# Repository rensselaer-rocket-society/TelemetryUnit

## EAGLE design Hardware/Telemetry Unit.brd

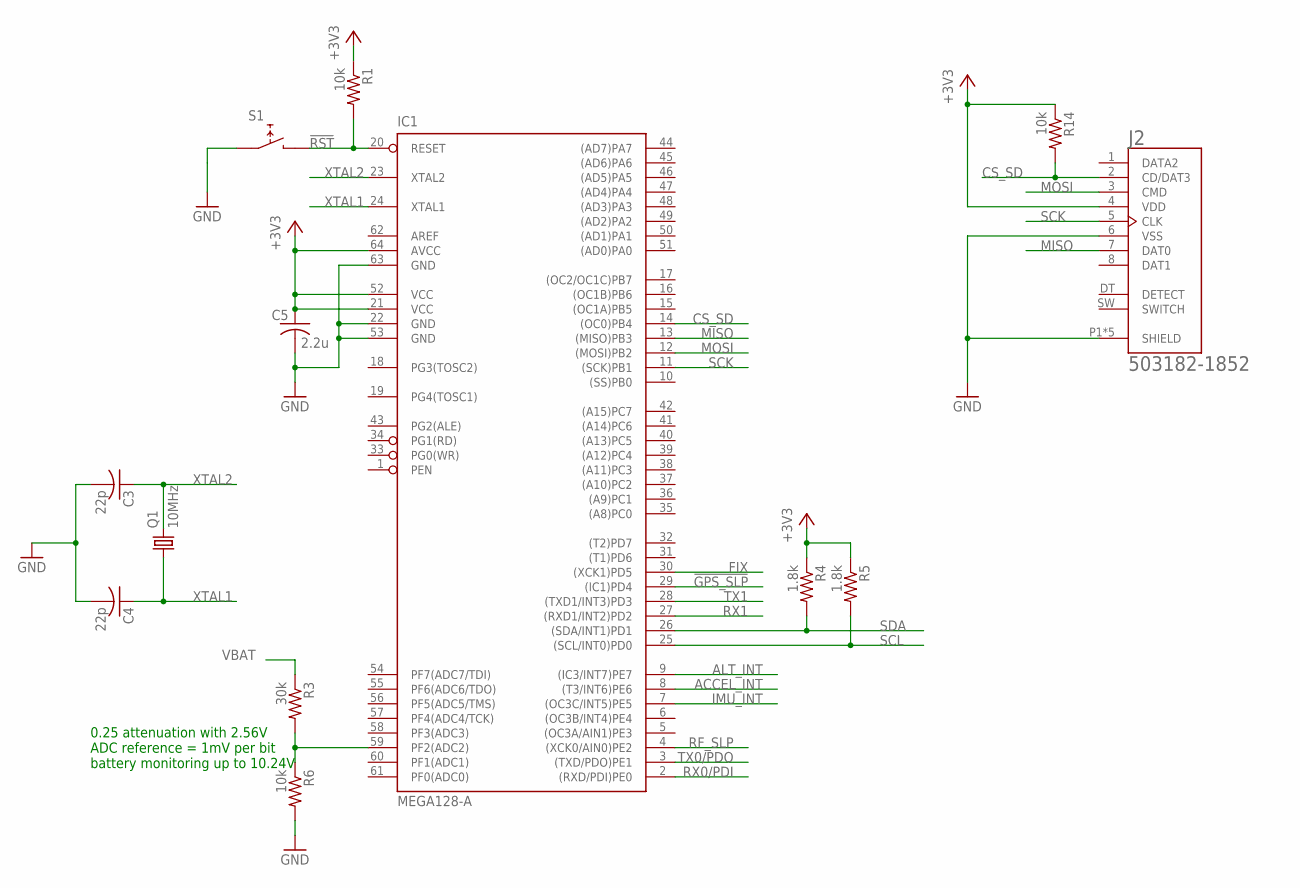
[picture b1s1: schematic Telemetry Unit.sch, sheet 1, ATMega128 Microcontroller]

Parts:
C3, C4: 22p; C0603
C5: 2.2u; C0603
IC1: MEGA128-A; TQFP64
J2: 503182-1852; MOLEX_503182-1852
Q1: 10MHz; 3.2X2.5_KX-7
R1, R6, R14: 10k; R0603
R3: 30k; R0603
R4, R5: 1.8k; R0603
S1: TACT_SW_4.5MM

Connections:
!GPS_SLP: IC1.29 ((IC1)PD4); also elsewhere on the board
!RST: IC1.20 (RESET), R1.2, S1.P2@1 (1), S1.P2@2 (1); also elsewhere on the board
+3V3: C5.1, IC1.21 (VCC), IC1.52 (VCC), IC1.64 (AVCC), J2.4 (VDD), R1.1, R4.1, R5.1, R14.1; also elsewhere on the board
ACCEL_INT: IC1.8 ((T3/INT6)PE6); also elsewhere on the board
ALT_INT: IC1.9 ((IC3/INT7)PE7); also elsewhere on the board
CS_SD: IC1.14 ((OC0)PB4), J2.2 (CD/DAT3), R14.2
FIX: IC1.30 ((XCK1)PD5); also elsewhere on the board
GND: C3.2, C4.2, C5.2, IC1.22 (GND), IC1.53 (GND), IC1.63 (GND), J2.6 (VSS), J2.P1 (SHIELD), J2.P2 (SHIELD), J2.P3 (SHIELD), J2.P4 (SHIELD), J2.P5 (SHIELD), R6.2, S1.P1@1 (0), S1.P1@2 (0); also elsewhere on the board
IMU_INT: IC1.7 ((OC3C/INT5)PE5); also elsewhere on the board
MISO: IC1.13 ((MISO)PB3), J2.7 (DAT0)
MOSI: IC1.12 ((MOSI)PB2), J2.3 (CMD)
unnamed: IC1.59 (PF2(ADC2)), R3.2, R6.1
RF_SLP: IC1.4 ((XCK0/AIN0)PE2); also elsewhere on the board
RX0/PDI: IC1.2 ((RXD/PDI)PE0); also elsewhere on the board
RX1: IC1.27 ((RXD1/INT2)PD2); also elsewhere on the board
SCK: IC1.11 ((SCK)PB1), J2.5 (CLK); also elsewhere on the board
SCL: IC1.25 ((SCL/INT0)PD0), R5.2; also elsewhere on the board
SDA: IC1.26 ((SDA/INT1)PD1), R4.2; also elsewhere on the board
TX0/PDO: IC1.3 ((TXD/PDO)PE1); also elsewhere on the board
TX1: IC1.28 ((TXD1/INT3)PD3); also elsewhere on the board
VBAT: R3.1; also elsewhere on the board
XTAL1: C4.1, IC1.24 (XTAL1), Q1.1
XTAL2: C3.1, IC1.23 (XTAL2), Q1.3 (2)

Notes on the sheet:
0.25 attenuation with 2.56V ADC reference = 1mV per bit battery monitoring up to 10.24V

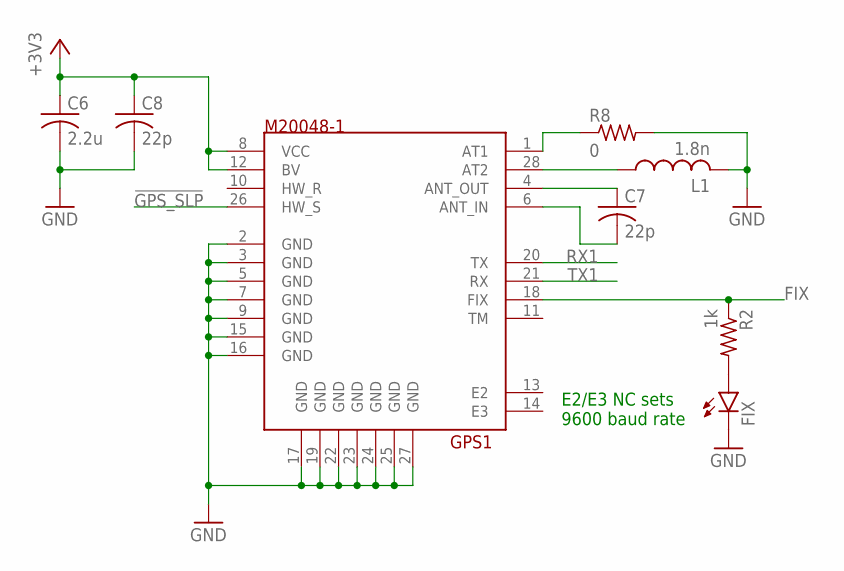
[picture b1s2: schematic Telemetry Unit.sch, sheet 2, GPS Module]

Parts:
C6: 2.2u; C0603
C7, C8: 22p; C0603
FIX: LEDCHIP-LED0603; CHIP-LED0603
GPS1: M20048-1
L1: 1.8n; L0603
R2: 1k; R0603
R8: 0; R0603

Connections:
!GPS_SLP: GPS1.26 (HW_S); also elsewhere on the board
+3V3: C6.1, C8.1, GPS1.8 (VCC), GPS1.12 (BV); also elsewhere on the board
FIX: GPS1.18 (FIX), R2.1; also elsewhere on the board
GND: C6.2, C8.2, FIX.C, GPS1.2 (GND), GPS1.3 (GND), GPS1.5 (GND), GPS1.7 (GND), GPS1.9 (GND), GPS1.15 (GND), GPS1.16 (GND), GPS1.17 (GND), GPS1.19 (GND), GPS1.22 (GND), GPS1.23 (GND), GPS1.24 (GND), GPS1.25 (GND), GPS1.27 (GND), L1.2, R8.2; also elsewhere on the board
unnamed: C7.1, GPS1.4 (ANT_OUT)
unnamed: C7.2, GPS1.6 (ANT_IN)
unnamed: GPS1.28 (AT2), L1.1
unnamed: FIX.A, R2.2
unnamed: GPS1.1 (AT1), R8.1
RX1: GPS1.20 (TX); also elsewhere on the board
TX1: GPS1.21 (RX); also elsewhere on the board

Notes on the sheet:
E2/E3 NC sets 9600 baud rate

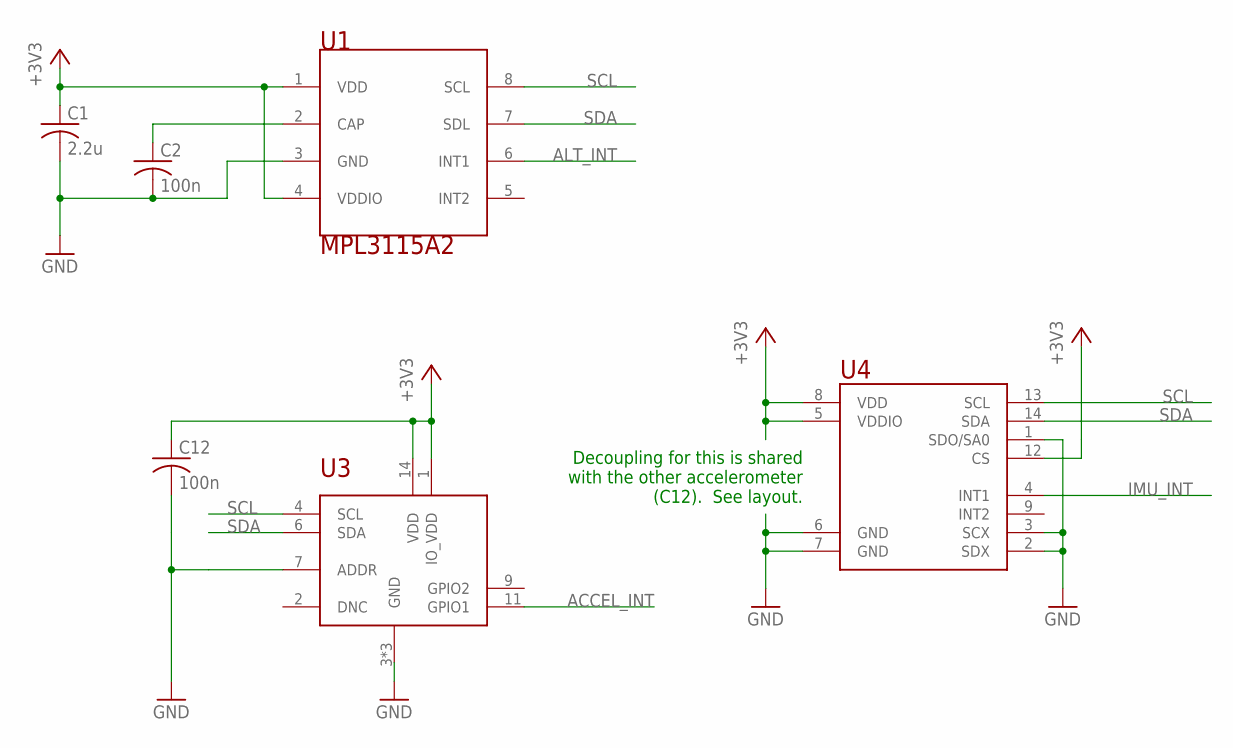
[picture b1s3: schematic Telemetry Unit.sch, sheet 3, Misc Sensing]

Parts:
C1: 2.2u; C0603
C2, C12: 100n; C0603
U1: MPL3115A2; LGA8
U3: KMX63-1055; LGA16_3X3
U4: LSM6DS3; 14-LGA

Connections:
+3V3: C1.1, C12.1, U1.1 (VDD), U1.4 (VDDIO), U3.1 (IO_VDD), U3.14 (VDD), U4.5 (VDDIO), U4.8 (VDD), U4.12 (CS); also elsewhere on the board
ACCEL_INT: U3.11 (GPIO1); also elsewhere on the board
ALT_INT: U1.6 (INT1); also elsewhere on the board
GND: C1.2, C2.2, C12.2, U1.3 (GND), U3.3 (GND), U3.5 (GND), U3.7 (ADDR), U3.12 (GND), U4.1 (SDO/SA0), U4.2 (SDX), U4.3 (SCX), U4.6 (GND), U4.7 (GND); also elsewhere on the board
IMU_INT: U4.4 (INT1); also elsewhere on the board
unnamed: C2.1, U1.2 (CAP)
SCL: U1.8 (SCL), U3.4 (SCL), U4.13 (SCL); also elsewhere on the board
SDA: U1.7 (SDL), U3.6 (SDA), U4.14 (SDA); also elsewhere on the board

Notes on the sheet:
Decoupling for this is shared with the other accelerometer (C12). See layout.

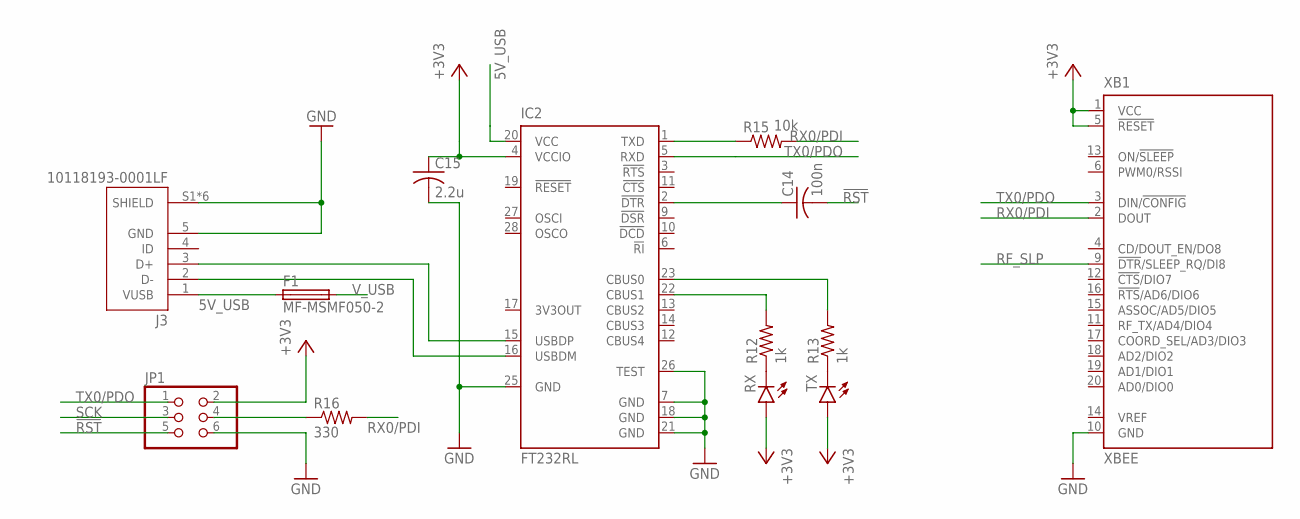
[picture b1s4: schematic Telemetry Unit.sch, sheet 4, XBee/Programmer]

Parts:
C14: 100n; C0603
C15: 2.2u; C0603
F1: MF-MSMF050-2; FUSM1812X02
IC2: FT232RL; SSOP28
J3: 10118193-0001LF; FCI_10118193-0001LF
JP1: PINHD-2X3; 2X03
R12, R13: 1k; R0603
R15: 10k; R0603
R16: 330; R0603
RX: LEDCHIP-LED0603; CHIP-LED0603
TX: LEDCHIP-LED0603; CHIP-LED0603
XB1: XBEE

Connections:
5V_USB: F1.1, IC2.20 (VCC), J3.1 (VUSB)
!RST: C14.2, JP1.5; also elsewhere on the board
+3V3: C15.1, IC2.4 (VCCIO), JP1.2, RX.A, TX.A, XB1.1 (VCC), XB1.5 (!RESET); also elsewhere on the board
GND: C15.2, IC2.7 (GND), IC2.18 (GND), IC2.21 (GND), IC2.25 (GND), IC2.26 (TEST), J3.5 (GND), J3.S1 (SHIELD), J3.S2 (SHIELD), J3.S3 (SHIELD), J3.S4 (SHIELD), J3.S5 (SHIELD), J3.S6 (SHIELD), JP1.6, XB1.10 (GND); also elsewhere on the board
unnamed: IC2.16 (USBDM), J3.2 (D-)
unnamed: IC2.15 (USBDP), J3.3 (D+)
unnamed: R12.1, RX.C
unnamed: C14.1, IC2.2 (!DTR)
unnamed: R13.1, TX.C
unnamed: IC2.22 (CBUS1), R12.2
unnamed: IC2.23 (CBUS0), R13.2
unnamed: IC2.1 (TXD), R15.1
PDI: JP1.4, R16.1
RF_SLP: XB1.9 (!DTR!/SLEEP_RQ/DI8); also elsewhere on the board
RX0/PDI: R15.2, R16.2, XB1.2 (DOUT); also elsewhere on the board
SCK: JP1.3; also elsewhere on the board
TX0/PDO: IC2.5 (RXD), JP1.1, XB1.3 (DIN/!CONFIG); also elsewhere on the board
V_USB: F1.2; also elsewhere on the board

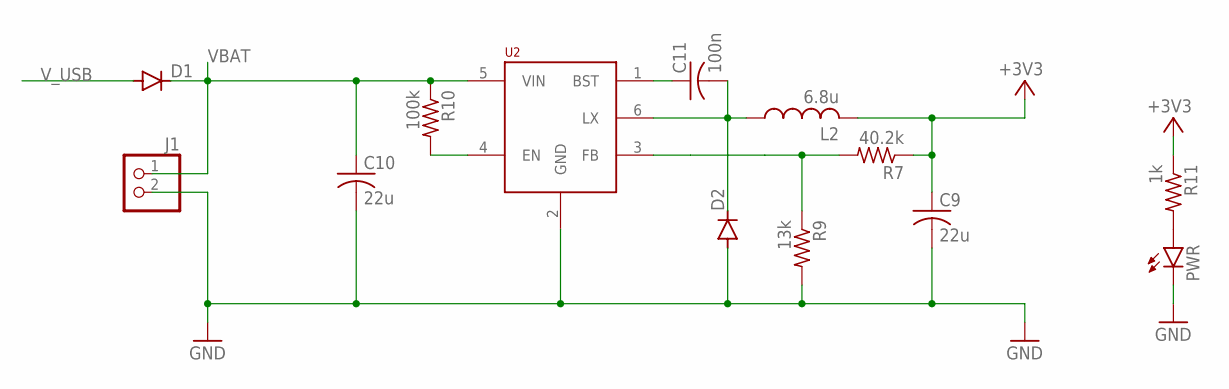
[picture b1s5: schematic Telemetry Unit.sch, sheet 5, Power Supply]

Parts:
C9, C10: 22u; C0805
C11: 100n; C0603
D1, D2: DIODE-SOD123; SOD123
J1: ST_2X1
L2: 6.8u; L1210
PWR: LEDCHIP-LED0603; CHIP-LED0603
R7: 40.2k; R0603
R9: 13k; R0603
R10: 100k; R0603
R11: 1k; R0603
U2: AOZ1280; TSOT23-6

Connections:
+3V3: C9.1, L2.2, R7.1, R11.1; also elsewhere on the board
GND: C9.2, C10.2, D2.A, J1.2, PWR.C, R9.2, U2.2 (GND); also elsewhere on the board
unnamed: C11.2, D2.C, L2.1, U2.6 (LX)
unnamed: R10.2, U2.4 (EN)
unnamed: R7.2, R9.1, U2.3 (FB)
unnamed: C11.1, U2.1 (BST)
unnamed: PWR.A, R11.2
VBAT: C10.1, D1.C, J1.1, R10.1, U2.5 (VIN); also elsewhere on the board
V_USB: D1.A; also elsewhere on the board

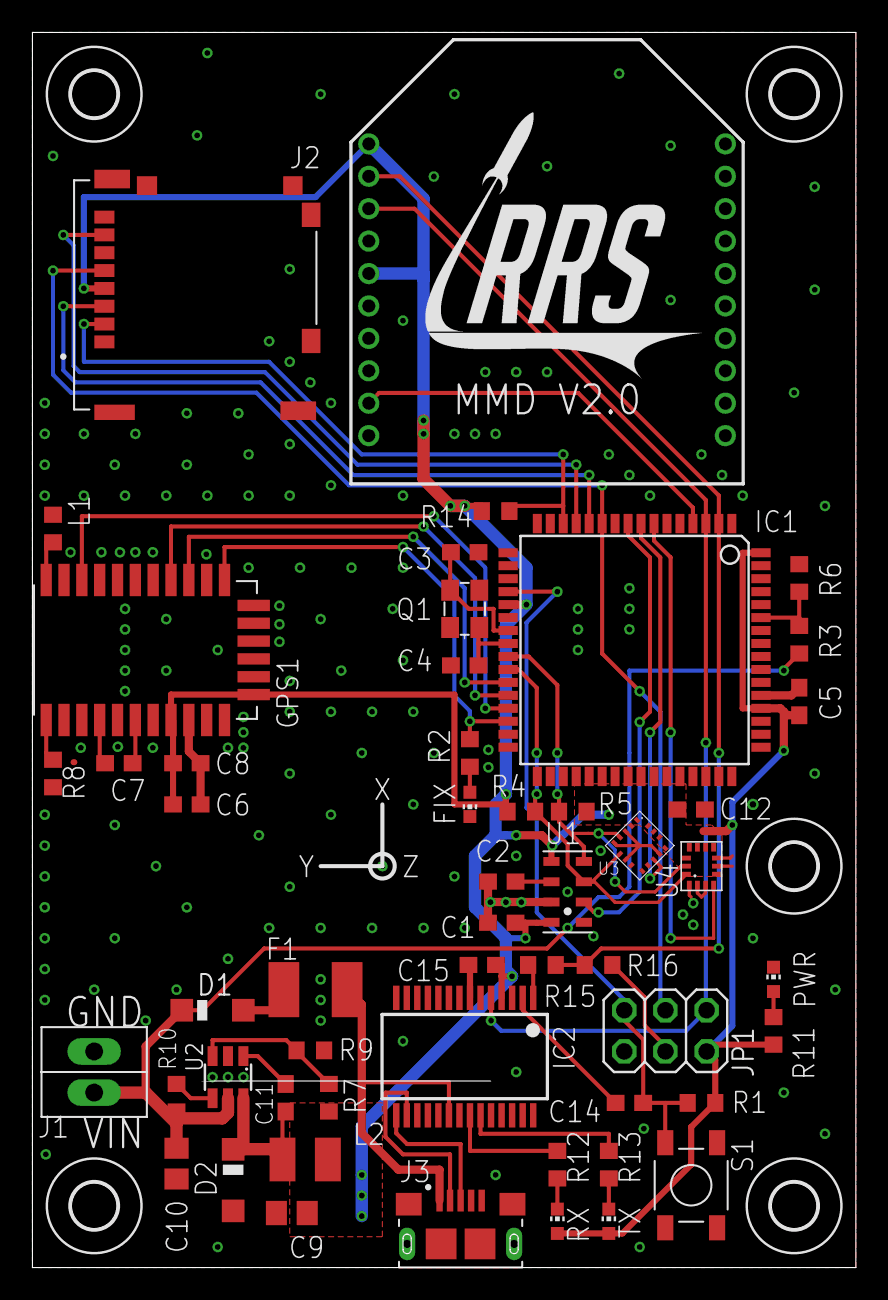
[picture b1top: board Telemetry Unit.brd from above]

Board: 2 copper layers, 50.8 x 76.2 mm, 58 parts (0 on the bottom side), 45 nets.

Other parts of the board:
U$1, U$2, U$3, U$4, U$5: 2,8

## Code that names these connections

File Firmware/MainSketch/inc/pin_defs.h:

// Useful pin numbers (see Pin Mapping Table/64-pin-avr pins_arduino.h in MegaCore)
#define PIN_V_BAT		47
#define PIN_XBEE_RX		0
#define PIN_XBEE_TX		1
#define PIN_RF_SLP		2
#define PIN_IMU_INT		5
#define PIN_ACCEL_INT	6
#define PIN_ALT_INT		7
#define PIN_I2C_SCL		18
#define PIN_I2C_SDA		19
#define PIN_GPS_RX		20
#define PIN_GPS_TX		21
#define PIN_GPS_WAKE	22
#define PIN_FIX			23
#define PIN_SPI_SCK		9
#define PIN_SPI_MOSI	10
#define PIN_SPI_MISO	11
#define PIN_CS_SD		12

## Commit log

2019-01-27 First Pass at Compact Layout
2019-01-29 Switch to screw terminals for battery
2019-01-31 Add accelerometer
2019-02-01 Preliminary Signal Routing
2019-02-01 Apparently hadn't completely saved
2019-02-01 Merging changes into schematics.
2019-02-02 Finished merge, updated layout, added ICSP
2019-02-03 Full Routing Complete?
2019-02-03 Fix USB port nonsense/xBee logo
2019-02-03 Removed via
2019-02-05 Added fuse to usb
2019-02-05 Consolidated resistors and capacitors
2019-02-07 Reroute replaced components and add logo
2019-02-19 Create Arduino Sketch
2019-02-19 Timer2 Configuration
2019-02-19 Minimal OpenMCT Build
2019-02-19 Barebones Websocket Server
2019-02-19 Somewhat viable OpenMCT config
2019-02-19 Update to Python 3 and slow mock updates for sanity
2019-02-20 Organize data streams, make some actual plots
2019-02-21 Added packet support.
2019-02-21 New bootloader + GPS support?
2019-03-23 First pass at I2C UNTESTED
2019-03-24 Debugged I2C, Configure Output and Input pins
2019-03-25 Add modified boards.txt to git, set analog voltage reference
2019-03-28 Updated packet
2019-03-28 Integrate Packet Serial into Firmware (UNTESTED)
2019-04-09 Packet Serial Fixes + SD First Pass
2019-04-16 Finish basic implementation of historical telemetry
2019-05-15 Persist to disk endpoint, added Time Conductor for user timebase control. View-only mode from persited flight log
2019-05-17 Packet decoding software from binary logfile
2019-05-18 Fixed CRC byte position
2019-05-18 Switch PacketDecoder to real serial port, add temperature logging/streaming
2019-05-18 Optimization and log cleanup
2019-06-02 Save Button, Increased Baud Rate, Serial Error Correction, Favicon
2019-06-03 Do CRC check correctly
2019-06-08 CRC fixes and compatible SD logs
2019-06-09 Most minor updates and some rerouting
2019-06-09 New diode, layer cleanup, update silk
2019-06-09 Replace voltage regulator, reroute all
2019-06-15 Altimeter fixed, battery packets, timestamps, transmit fixed point for smaller packet size
2019-06-21 Beginning of Kalman Filter
2019-06-21 Re-enable SD logging in append mode
2019-06-28 Log processing scripts
2019-07-09 Larger board, fix GPS/SD placement
2019-07-10 Wide-Range Accelerometer
2019-07-10 Re-route power
2019-07-11 Reroute remianing signals and stitch grounds
2019-07-11 0 Ohm Tuning Resistor
2019-08-03 Move GPS to long edge. Much rerouting. Shrunk board 0.25"
2019-08-03 Update EAGLE and improve silkscreen
2019-08-03 Stitching vias for rest of board
2019-09-06 Add support for realtime replay of old log data
2019-09-18 Switch Accelerometer
2019-09-19 Add ability to generate files for each sensor series
2019-09-19 Ignore data analysis folder
2019-09-26 Layout accelerometers
2019-09-28 Removed old comment which was no longer relevant
2019-10-03 Final Rev 2
2019-10-16 Board/Stencil Order Receipts
2019-10-17 Create updated pin mapping header
2019-10-31 Preliminary Firmware for new accel
2020-02-13 Fix extra newline problem with series separator
2020-02-19 Setup Separate Custom Board Definition, More Descriptive Sketch Name
    Make it far easier for others to configure their environment to work with the tracker
2020-02-28 Get minimally working with new hardware
2020-03-03 Added test flight data folder w/ data from L3 flight
2023-05-01 Bump flask from 1.0.2 to 2.3.2 in /Ground Station
    Bumps [flask](https://github.com/pallets/flask) from 1.0.2 to 2.3.2.
    - [Release notes](https://github.com/pallets/flask/releases)
    - [Changelog](https://github.com/pallets/flask/blob/main/CHANGES.rst)
    - [Commits](https://github.com/pallets/flask/compare/1.0.2...2.3.2)
    ---
    updated-dependencies:

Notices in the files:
parts and their libraries:
crystal-geyer_V1_0: Copyright: Geyer-Electronic
